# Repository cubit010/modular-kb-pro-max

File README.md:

# KB ULTRA PRO MAX EXTREME
> [!NOTE]
> This project has been on the backburner for a while, as I decided to opt to develop a custom devboard for the microcontroller
> 
> However developing that devboard resulted in a footprint that will likely be too large to fit into the footprint of the keyboard, so I will be exploring options to have everything be directly on the board of the keyboard

Annnnyways

This project is a keyboard that has the potential to have many different modules attached, modules such as displays, a rotary encoder panel, potentiometers, or a numpad!
> [!NOTE]
> Most of the features can be added due to modularity, but will not be developed by me personally

## Communication interface
The core concept of modularity comes down to 1 main factor, and that is the compatibility of the communication interface.
I2c is chosen for its ability to have multiple devices share the same signal lines, high support by many microcontrollers, and a decently high signal rate for information

## Module development expectations

### Schematic

### PCB progress

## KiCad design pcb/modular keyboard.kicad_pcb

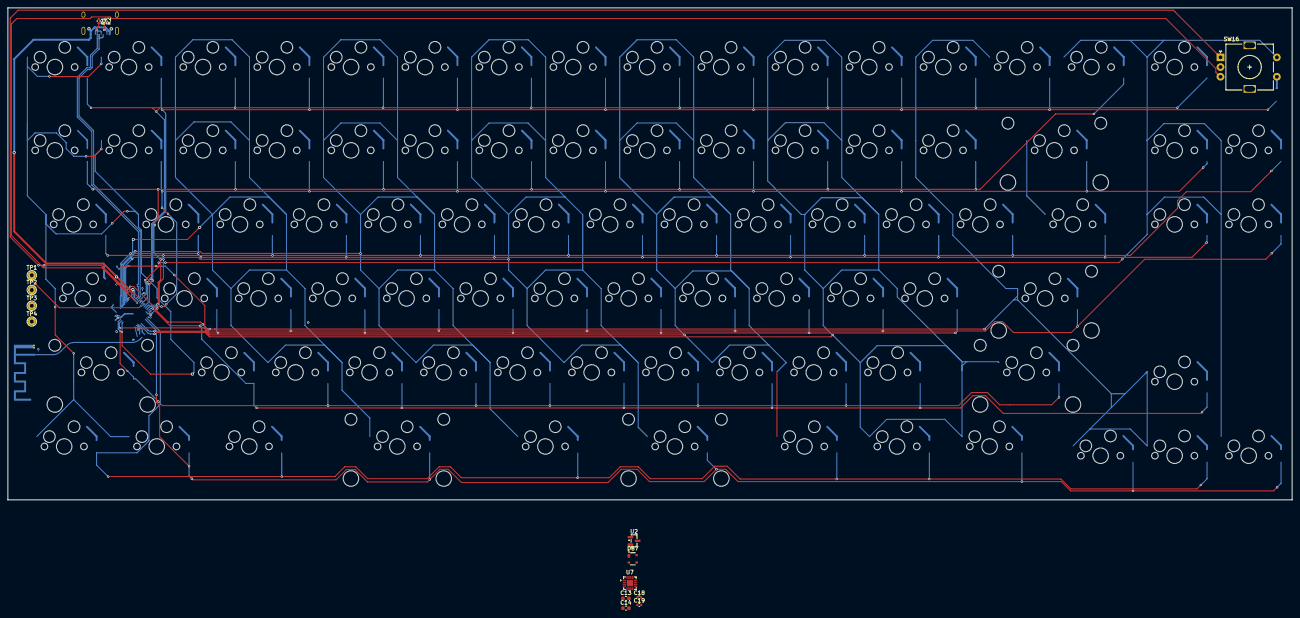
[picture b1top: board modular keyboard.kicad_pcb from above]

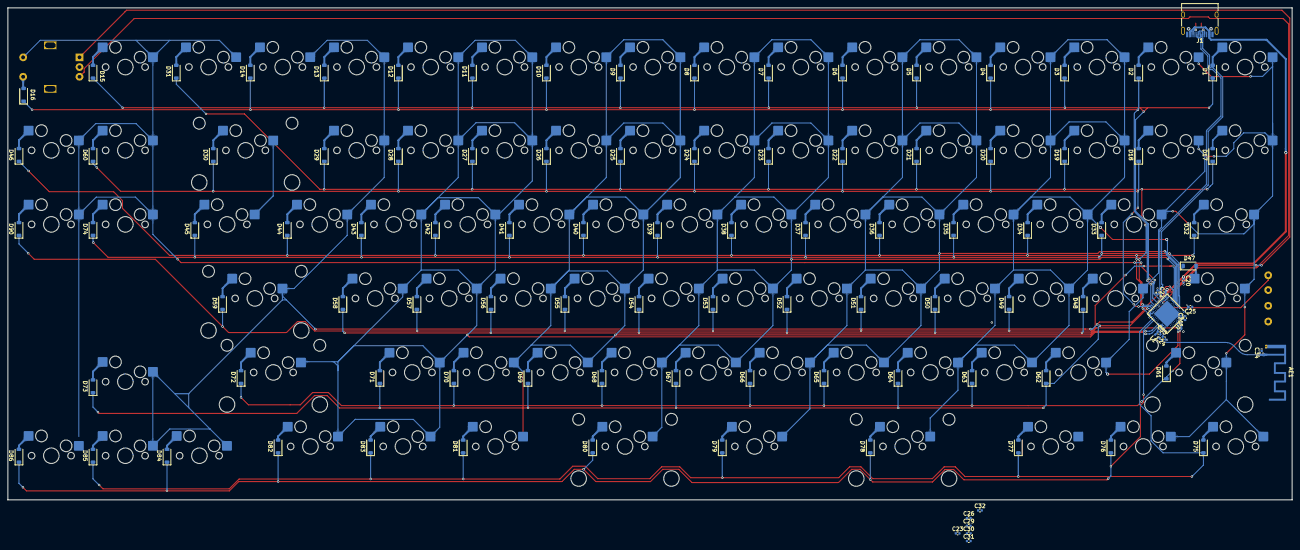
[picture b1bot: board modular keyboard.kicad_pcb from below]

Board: 4 copper layers, 330.5 x 126.6 mm, 204 parts (190 on the bottom side), 133 nets.

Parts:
AE1: Antenna_Shield; Texas_SWRA117D_2.4GHz_Right
C13, C14: 10uF; C_0603_1608Metric
C18, C19, C31, C32: 12pF; C_0402_1005Metric
C20, C22, C29: 4.7uF; C_0402_1005Metric
C21, C25, C26, C30: 1uF; C_0402_1005Metric
C23: 100nF; C_0402_1005Metric
C24: 100pF; C_0402_1005Metric
C33: 0.8pF; C_0402_1005Metric
C34: 0.5pF; C_0402_1005Metric
D1, D2, D3, D4, D5, D6, D7, D8, D9, D10, D11, D12, D13, D14, D15, D16, D17, D18, D19, D20, D21, D22, D23, D24, D25, D26, D27, D28, D29, D30, D31, D32, D33, D34, D35, D36, D37, D38, D39, D40, D41, D42, D43, D44, D45, D46, D47, D48, D49, D50, D51, D52, D53, D54, D55, D56, D57, D58, D59, D60, D61, D62, D63, D64, D65, D66, D67, D68, D69, D70, D71, D72, D73, D74, D75, D76, D77, D78, D79, D80, D81, D82, D83, D84, D85, D86, D90: 1N4148W; D_SOD-123
D87: PRTR5V0U2X; SOT-143
J1: USB_C_Receptacle_USB2.0_14P; USB_C_Receptacle_HRO_TYPE-C-31-M-12
L1: 4.7nH; L_0402_1005Metric
R1, R2: 5.1K; R_0402_1005Metric
SW1, SW2, SW3, SW4, SW5, SW6, SW7, SW8, SW9, SW10, SW11, SW12, SW13, SW14, SW15, SW17, SW18, SW19, SW20, SW21, SW22, SW23, SW24, SW25, SW26, SW27, SW28, SW29, SW33, SW34, SW35, SW36, SW37, SW38, SW39, SW40, SW41, SW42, SW43, SW44, SW48, SW49, SW50, SW51, SW52, SW53, SW54, SW55, SW56, SW57, SW58, SW62, SW63, SW64, SW65, SW66, SW67, SW68, SW69, SW70, SW71, SW73, SW84, SW85, SW86: SW_Push_45deg; MX-Hotswap-1U
SW16: RotaryEncoder_Switch; RotaryEncoder_Alps_EC11E-Switch_Vertical_H20mm
SW30: backsp2.0; MX-Hotswap-2U
SW31: Screenshot (row1); MX-Hotswap-1U
SW32: tab1.5; MX-Hotswap-1.5U
SW45: \1.5; MX-Hotswap-1.5U
SW46: home; MX-Hotswap-1U
SW47: caps1.75; MX-Hotswap-1.75U
SW59: enter2.25; MX-Hotswap-2.25U
SW60: pgup; MX-Hotswap-1U
SW61: Lshift2.25; MX-Hotswap-2.25U
SW72: Rshift2.75; MX-Hotswap-2.75U
SW74: pgdn; MX-Hotswap-1U
SW75: Lctrl1.25; MX-Hotswap-1.25U
SW76: win1.25; MX-Hotswap-1.25U
SW77: Lalt1.25; MX-Hotswap-1.25U
SW78: Lspace2.75; MX-Hotswap-2.75U
SW79: Mspace1.25; MX-Hotswap-1.25U
SW80: Rspace2.25; MX-Hotswap-2.25U
SW81: Ralt1.25; MX-Hotswap-1.25U
SW82: Rctrl1.25; MX-Hotswap-1.25U
SW83: rFN1.25; MX-Hotswap-1.25U
SW87: end; MX-Hotswap-1U
TP1, TP2, TP3: TestPoint; TestPoint_THTPad_D2.0mm_Drill1.0mm
TP4: GND contact; TestPoint_THTPad_D2.0mm_Drill1.0mm
U2: MCP1700x-300xxTT; SOT-23
U4: nRF52840; Nordic_AQFN-73-1EP_7x7mm_P0.5mm
U7: BQ24075RGT; VQFN-16-1EP_3x3mm_P0.5mm_EP1.6x1.6mm

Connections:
+3V3: C13.1, U2.2 (VO)
/mainboard/USB_D+: D87.3 (I/O2), J1.A6 (D+), J1.B6 (D+), U4.AD6 (D+)
/mainboard/USB_D-: D87.2 (I/O1), J1.A7 (D-), J1.B7 (D-), U4.AD4 (D-)
A: SW16.A, U4.AD10 (P0.15)
B: SW16.B, U4.AC9 (P0.14)
Col1: SW1.1, SW2.1, SW17.1, SW18.1, SW32.1, SW33.1, SW47.1, SW48.1, SW61.1, SW62.1, SW75.1, SW76.1, U4.A12 (AIN0/P0.02)
Col2: SW3.1, SW4.1, SW19.1, SW20.1, SW34.1, SW35.1, SW49.1, SW50.1, SW63.1, SW64.1, SW78.1, U4.J1 (AIN2/P0.04)
Col3: SW5.1, SW6.1, SW21.1, SW22.1, SW36.1, SW37.1, SW51.1, SW52.1, SW65.1, SW66.1, SW79.1, U4.L1 (P0.06)
Col4: SW7.1, SW8.1, SW23.1, SW24.1, SW38.1, SW39.1, SW53.1, SW54.1, SW67.1, SW68.1, SW80.1, U4.N1 (P0.08)
Col5: SW9.1, SW10.1, SW25.1, SW26.1, SW40.1, SW41.1, SW55.1, SW56.1, SW69.1, SW70.1, SW81.1, U4.L24 (NFC1/P0.09)
Col6: SW11.1, SW12.1, SW27.1, SW28.1, SW42.1, SW43.1, SW57.1, SW58.1, SW71.1, SW72.1, SW82.1, SW83.1, U4.J24 (NFC2/P0.10)
Col7: SW13.1, SW14.1, SW29.1, SW30.1, SW44.1, SW45.1, SW59.1, SW73.1, SW84.1, SW85.1, U4.U1 (TRACEDATA1/P0.12)
Col8: SW15.1, SW16.S2, SW31.1, SW46.1, SW60.1, SW74.1, SW86.1, SW87.1, U4.AD8 (P0.13)
GND: AE1.2 (Shield), C13.2, C14.2, C18.1, C19.1, C20.2, C21.1, C22.1, C23.1, C24.1, C25.1, C26.2, C29.2, C30.2, C31.2, C32.2, C34.2, D87.1 (GND), J1.A1 (GND), J1.A12 (GND), J1.B1 (GND), J1.B12 (GND), J1.S1 (SHIELD), R1.1, R2.1, SW16.C, TP4.1, U2.1 (GND), U4.B7 (VSS), U4.EP (VSS), U7.4 (~CE), U7.5 (EN2), U7.8 (VSS), U7.15 (SYSOFF), U7.17 (VSS)
unnamed: AE1.1 (A), C34.1, L1.1
unnamed: D1.2 (A), SW1.2
unnamed: D2.2 (A), SW2.2
unnamed: D3.2 (A), SW3.2
unnamed: D4.2 (A), SW4.2
unnamed: D5.2 (A), SW5.2
unnamed: D6.2 (A), SW6.2
unnamed: D7.2 (A), SW7.2
unnamed: D8.2 (A), SW8.2
unnamed: D9.2 (A), SW9.2
unnamed: D10.2 (A), SW10.2
unnamed: D11.2 (A), SW11.2
unnamed: D12.2 (A), SW12.2
unnamed: D13.2 (A), SW13.2
unnamed: D14.2 (A), SW14.2
unnamed: D15.2 (A), SW15.2
unnamed: D16.2 (A), SW16.S1
unnamed: D17.2 (A), SW17.2
unnamed: D18.2 (A), SW18.2
unnamed: D19.2 (A), SW19.2
unnamed: D20.2 (A), SW20.2
unnamed: D21.2 (A), SW21.2
unnamed: D22.2 (A), SW22.2
unnamed: D23.2 (A), SW23.2
unnamed: D24.2 (A), SW24.2
unnamed: D25.2 (A), SW25.2
unnamed: D26.2 (A), SW26.2
unnamed: D27.2 (A), SW27.2
unnamed: D28.2 (A), SW28.2
unnamed: D29.2 (A), SW29.2
unnamed: D30.2 (A), SW30.2
unnamed: D31.2 (A), SW31.2
unnamed: D32.2 (A), SW32.2
unnamed: D33.2 (A), SW33.2
unnamed: D34.2 (A), SW34.2
unnamed: D35.2 (A), SW35.2
unnamed: D36.2 (A), SW36.2
unnamed: D37.2 (A), SW37.2
unnamed: D38.2 (A), SW38.2
unnamed: D39.2 (A), SW39.2
unnamed: D40.2 (A), SW40.2
unnamed: D41.2 (A), SW41.2
unnamed: D42.2 (A), SW42.2
unnamed: D43.2 (A), SW43.2
unnamed: D44.2 (A), SW44.2
unnamed: D45.2 (A), SW45.2
unnamed: D46.2 (A), SW46.2
unnamed: D47.2 (A), SW47.2
unnamed: D48.2 (A), SW48.2
unnamed: D49.2 (A), SW49.2
unnamed: D50.2 (A), SW50.2
unnamed: D51.2 (A), SW51.2
unnamed: D52.2 (A), SW52.2
unnamed: D53.2 (A), SW53.2
unnamed: D54.2 (A), SW54.2
unnamed: D55.2 (A), SW55.2
unnamed: D56.2 (A), SW56.2
unnamed: D57.2 (A), SW57.2
unnamed: D58.2 (A), SW58.2
unnamed: D59.2 (A), SW59.2
unnamed: D60.2 (A), SW60.2
unnamed: D61.2 (A), SW61.2
unnamed: D62.2 (A), SW62.2
unnamed: D63.2 (A), SW63.2
unnamed: D64.2 (A), SW64.2
unnamed: D65.2 (A), SW65.2
unnamed: D66.2 (A), SW66.2
unnamed: D67.2 (A), SW67.2
unnamed: D68.2 (A), SW68.2
unnamed: D69.2 (A), SW69.2
unnamed: D70.2 (A), SW70.2
unnamed: D71.2 (A), SW71.2
unnamed: D72.2 (A), SW72.2
unnamed: D73.2 (A), SW73.2
unnamed: D74.2 (A), SW74.2
unnamed: D75.2 (A), SW75.2
unnamed: D76.2 (A), SW76.2
unnamed: D77.2 (A), SW77.2
unnamed: D78.2 (A), SW78.2
unnamed: D79.2 (A), SW79.2
unnamed: D80.2 (A), SW80.2
unnamed: D81.2 (A), SW81.2
unnamed: D82.2 (A), SW82.2
unnamed: D83.2 (A), SW83.2
unnamed: D84.2 (A), SW84.2
unnamed: D85.2 (A), SW85.2
unnamed: D86.2 (A), SW86.2
unnamed: D90.2 (A), SW87.2
unnamed: J1.A5 (CC1), R1.2
unnamed: J1.B5 (CC2), R2.2
unnamed: C33.1, L1.2, U4.H23 (ANT)
unnamed: C23.2, U4.C1 (DEC1)
unnamed: C24.2, U4.D23 (DEC3)
unnamed: C21.2, U4.B5 (DEC4), U4.E24 (DEC6)
unnamed: C22.2, U4.AC5 (DECUSB)
unnamed: TP1.1, U4.AC13 (P0.18/~RESET)
unnamed: TP2.1, U4.AA24 (SWDCLK)
unnamed: TP3.1, U4.AC24 (SWDIO)
unnamed: C19.2, U4.B24 (XC1)
unnamed: C18.2, U4.A23 (XC2)
unnamed: C31.1, U4.D2 (XL1/P0.00)
unnamed: C32.1, U4.F2 (XL2/P0.01)
Row1: D1.1 (K), D3.1 (K), D5.1 (K), D7.1 (K), D9.1 (K), D11.1 (K), D13.1 (K), D15.1 (K), U4.AD12 (P0.17)
Row2: D2.1 (K), D4.1 (K), D6.1 (K), D8.1 (K), D10.1 (K), D12.1 (K), D14.1 (K), D16.1 (K), U4.AD16 (P0.20)
Row3: D17.1 (K), D19.1 (K), D21.1 (K), D23.1 (K), D25.1 (K), D27.1 (K), D29.1 (K), D31.1 (K), U4.AD18 (P0.22)
Row4: D18.1 (K), D20.1 (K), D22.1 (K), D24.1 (K), D26.1 (K), D28.1 (K), D30.1 (K), D60.1 (K), U4.AD20 (P0.24)
Row5: D32.1 (K), D34.1 (K), D36.1 (K), D38.1 (K), D40.1 (K), D42.1 (K), D44.1 (K), D46.1 (K), U4.AC21 (P0.25)
Row6: D33.1 (K), D35.1 (K), D37.1 (K), D39.1 (K), D41.1 (K), D43.1 (K), D45.1 (K), D74.1 (K), U4.G1 (P0.26)
Row7: D47.1 (K), D49.1 (K), D51.1 (K), D53.1 (K), D55.1 (K), D57.1 (K), D59.1 (K), D90.1 (K), U4.R1 (TRACEDATA3/P1.09)
Row8: D48.1 (K), D50.1 (K), D52.1 (K), D54.1 (K), D56.1 (K), D58.1 (K), U4.A10 (AIN5/P0.29)
Row9: D61.1 (K), D63.1 (K), D65.1 (K), D66.1 (K), D68.1 (K), D70.1 (K), D72.1 (K), U4.A8 (AIN7/P0.31)
Row10: D62.1 (K), D64.1 (K), D67.1 (K), D69.1 (K), D71.1 (K), D73.1 (K), U4.AD22 (TRACEDATA0/P1.00)
Row11: D75.1 (K), D77.1 (K), D79.1 (K), D81.1 (K), D83.1 (K), D85.1 (K), U4.W24 (P1.02)
Row12: D76.1 (K), D78.1 (K), D80.1 (K), D82.1 (K), D84.1 (K), D86.1 (K), U4.U24 (P1.04)
VBAT: U4.Y2 (VDDH), U7.2 (BAT), U7.3 (BAT)
VBUS: C14.1, C20.1, C30.1, D87.4 (VCC), J1.A4 (VBUS), J1.A9 (VBUS), J1.B4 (VBUS), J1.B9 (VBUS), U2.3 (VI), U4.AD2 (VBUS), U7.13 (IN)
VDD nRF / 3v3: C25.2, C26.1, U4.A22 (VDD), U4.AD14 (VDD), U4.AD23 (VDD), U4.B1 (VDD), U4.W1 (VDD)
VDDH: C29.1, U7.6 (EN1), U7.10 (OUT), U7.11 (OUT)
VSS_PA: C33.2, U4.F23 (VSS_PA)

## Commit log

2026-04-01 adding current files
2026-04-01 started working on the readme
    first time actually trying on making a good readme, with good markdown formatting
